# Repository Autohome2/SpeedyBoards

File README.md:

# SpeedyBoards
WTMtronics has developed several EMS PCBs designed to use the Speeduino firmware.
The Speeduino code is available here [Speeduino](https://github.com/noisymime/speeduino), but the easiest way to load the code onto your ECU is to use [SpeedyLoader](https://github.com/speeduino/SpeedyLoader).
## Ocelot
The latest ECU designed by WTMtronics builds on the UA4C that came before it, and in fact if you compare the two side by side you will see many similarities. However there have been many improvements over the previous model which are outlined in the list below.
- Automotive connector
- Reduced size
- Integrated microcontroller
- VSS input
- Flyback diodes
- Reset button

The reset button was added as the only reset connection made to the microcontroller to prevent unwanted resets from USB connected devices. There is a caveat to this arrangement though. While the first time a firmware is loaded it will go on without intervention, subsequent times will require the user to hold the reset button down then release the button when the program starts the upload process. If the upload does not start right away go back and try again.

The Ocelot uses the Silicon Labs CP2102N USB to UART controller chip. Most modern computers will detect and automatically load a driver for the COM port. If you are not getting the COM port, then you can download drivers from their website [Silicon Labs Drivers](https://www.silabs.com/developers/usb-to-uart-bridge-vcp-drivers).

Versions:

A4:
- Corrected USB chip power
- Changed to smaller USB chip
- Corrected trigger labeling
- Changed trigger jumpers to match other boards

A3:
- First release

### Errata
vA3:
- Labeling for trigger jumpers is reversed. The secondary trigger jumpers are nearest the outside edge of the board, and the primary trigger jumpers are near the trigger conditioner socket.
- Serial numbers prior to 002287 will not operate with out a USB connection if no Bluetooth adapter is attached. If your serial number is 002287 or higher this issue does not affect your unit. If you are affected by this issue, please contact us so we can help you [WTMtronics Help](https://wtmtronics.com/help).
## UA4C
The Under Arduino Four Channel was designed to be as small as possible wile still using a standard off the shelf Arduino MEGA and Hammond extruded enclosure. This was achieved by using SMD components and placing the Arduino upside-down on top of the PCB. The unique stacking arrangement allows the unit to be particularly thin for a unit that still uses a separate Arduino MEGA. It is a 4+4 board that incorporates the follow features.
- Four injector channels
- Four ignitor channels
- Outputs for VVT, 2x PWM idle, boost, fuel pump, tachometer, and 2x fan
- Four auxiliary outputs
- Built in stepper idle control (versions C)
- Two trigger inputs
- Launch input
- Two additional interrupt input designated as flex and knock*
- Analog inputs for CLT, IAT, TPS, and O2
- Two auxiliary analog inputs
- MAP and baro sensor onboard
- Two GPIO connections that breakout inside the case

Latest version: C6

*Knock is currently unsupported in the firmware. Either input can be used for VSS.
## NO2C
The No Overhang Two Channel was designed to incorporate as many features as possible into a through-hole board that does not exceed the dimensions of the Arduino MEGA microcontroller it sits on top of. It is a 2+2 channel board that incorporates the features below.
- Two injector channels
- Two ignitor channels
- Outputs for VVT PWM idle, boost, fuel pump, and tachometer
- Two trigger inputs
- Launch input
- Analog inputs for CLT, IAT, TPS, and O2
- MAP sensor onboard
- Socket for stepper idle control module

Latest version: D1

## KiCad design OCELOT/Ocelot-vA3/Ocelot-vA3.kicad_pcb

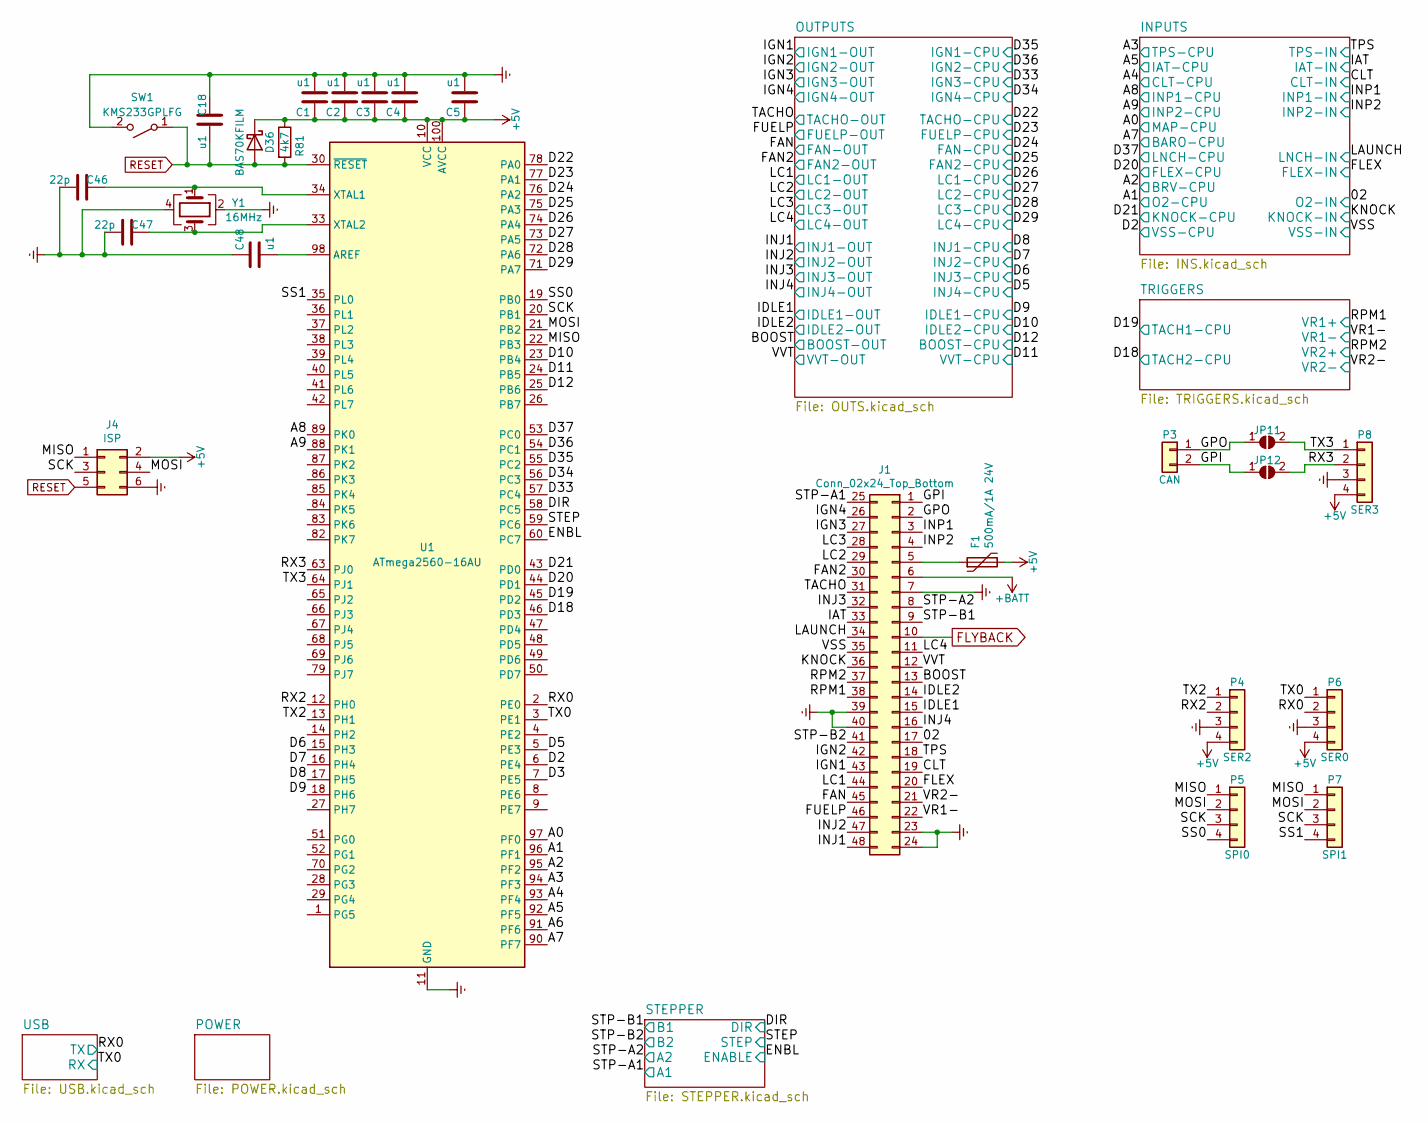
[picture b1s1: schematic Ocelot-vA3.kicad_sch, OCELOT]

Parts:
C1, C2, C3, C4, C5, C18, C48: u1; C_0603_1608Metric; MPN CL21B104KBFNNNE
C46, C47: 22p; C_0603_1608Metric
D36: BAS70KFILM; D_SOD-523; MPN BAS70-02V-V-G-08
F1: 500mA/1A 24V; Fuse_1206_3216Metric; MPN 0ZCJ0050AF2E
J1: Conn_02x24_Top_Bottom; JSA_ZRO_48_Black
J4: ISP; PinHeader_2x03_P2.54mm_Vertical
JP11, JP12: SolderJumper_2_Open; SolderJumper-2_P1.3mm_Open_Pad1.0x1.5mm; MPN DNP
P3: CAN; PinHeader_1x02_P2.54mm_Vertical; MPN DNP
P4: SER2; Pin_Header_Straight_1x04_Pitch2.54mm; MPN DNP
P5: SPI0; Pin_Header_Straight_1x04_Pitch2.54mm; MPN DNP
P6: SER0; Pin_Header_Straight_1x04_Pitch2.54mm; MPN DNP
P7: SPI1; Pin_Header_Straight_1x04_Pitch2.54mm; MPN DNP
P8: SER3; Pin_Header_Straight_1x04_Pitch2.54mm; MPN DNP
R81: 4k7; R_0603_1608Metric
SW1: KMS233GPLFG; SW_SPST_CK_KMS2xxGP
U1: ATmega2560-16AU; TQFP-100_14x14mm_P0.5mm
Y1: 16MHz; Crystal_SMD_3225-4Pin_3.2x2.5mm; MPN YSX321SL

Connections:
+5V: C1.1, C2.1, C3.1, C4.1, C5.1, D36.1 (K), F1.2, J4.2, P4.4, P6.4, P8.4, R81.1, U1.10 (VCC), U1.31 (VCC), U1.61 (VCC), U1.80 (VCC), U1.100 (AVCC); also elsewhere on the board
+BATT: J1.6; also elsewhere on the board
/02: J1.17; also elsewhere on the board
/A0: U1.97 (PF0); also elsewhere on the board
/A1: U1.96 (PF1); also elsewhere on the board
/A2: U1.95 (PF2); also elsewhere on the board
/A3: U1.94 (PF3); also elsewhere on the board
/A4: U1.93 (PF4); also elsewhere on the board
/A5: U1.92 (PF5); also elsewhere on the board
/A6: U1.91 (PF6)
/A7: U1.90 (PF7); also elsewhere on the board
/A8: U1.89 (PK0); also elsewhere on the board
/A9: U1.88 (PK1); also elsewhere on the board
/BOOST: J1.13; also elsewhere on the board
/CLT: J1.19; also elsewhere on the board
/D2: U1.6 (PE4); also elsewhere on the board
/D3: U1.7 (PE5)
/D5: U1.5 (PE3); also elsewhere on the board
/D6: U1.15 (PH3); also elsewhere on the board
/D7: U1.16 (PH4); also elsewhere on the board
/D8: U1.17 (PH5); also elsewhere on the board
/D9: U1.18 (PH6); also elsewhere on the board
/D10: U1.23 (PB4); also elsewhere on the board
/D11: U1.24 (PB5); also elsewhere on the board
/D12: U1.25 (PB6); also elsewhere on the board
/D18: U1.46 (PD3); also elsewhere on the board
/D19: U1.45 (PD2); also elsewhere on the board
/D20: U1.44 (PD1); also elsewhere on the board
/D21: U1.43 (PD0); also elsewhere on the board
/D22: U1.78 (PA0); also elsewhere on the board
/D23: U1.77 (PA1); also elsewhere on the board
/D24: U1.76 (PA2); also elsewhere on the board
/D25: U1.75 (PA3); also elsewhere on the board
/D26: U1.74 (PA4); also elsewhere on the board
/D27: U1.73 (PA5); also elsewhere on the board
/D28: U1.72 (PA6); also elsewhere on the board
/D29: U1.71 (PA7); also elsewhere on the board
/D33: U1.57 (PC4); also elsewhere on the board
/D34: U1.56 (PC3); also elsewhere on the board
/D35: U1.55 (PC2); also elsewhere on the board
/D36: U1.54 (PC1); also elsewhere on the board
/D37: U1.53 (PC0); also elsewhere on the board
/DIR: U1.58 (PC5); also elsewhere on the board
/ENBL: U1.60 (PC7); also elsewhere on the board
/FAN: J1.45; also elsewhere on the board
/FAN2: J1.30; also elsewhere on the board
/FLEX: J1.20; also elsewhere on the board
/FUELP: J1.46; also elsewhere on the board
/GPI: J1.1, JP12.1 (A), P3.2
/GPO: J1.2, JP11.1 (A), P3.1
/IAT: J1.33; also elsewhere on the board
/IDLE1: J1.15; also elsewhere on the board
/IDLE2: J1.14; also elsewhere on the board
/IGN1: J1.43; also elsewhere on the board
/IGN2: J1.42; also elsewhere on the board
/IGN3: J1.27; also elsewhere on the board
/IGN4: J1.26; also elsewhere on the board
/INJ1: J1.48; also elsewhere on the board
/INJ2: J1.47; also elsewhere on the board
/INJ3: J1.32; also elsewhere on the board
/INJ4: J1.16; also elsewhere on the board
/INP1: J1.3; also elsewhere on the board
/INP2: J1.4; also elsewhere on the board
/KNOCK: J1.36; also elsewhere on the board
/LAUNCH: J1.34; also elsewhere on the board
/LC1: J1.44; also elsewhere on the board
/LC2: J1.29; also elsewhere on the board
/LC3: J1.28; also elsewhere on the board
/LC4: J1.11; also elsewhere on the board
/MISO: J4.1, P5.1, P7.1, U1.22 (PB3)
/MOSI: J4.4, P5.2, P7.2, U1.21 (PB2)
/RPM1: J1.38; also elsewhere on the board
/RPM2: J1.37; also elsewhere on the board
/RX0: P6.2, U1.2 (PE0); also elsewhere on the board
/RX2: P4.2, U1.12 (PH0)
/RX3: JP12.2 (B), P8.2, U1.63 (PJ0)
/SCK: J4.3, P5.3, P7.3, U1.20 (PB1)
/SS0: P5.4, U1.19 (PB0)
/SS1: P7.4, U1.35 (PL0)
/STEP: U1.59 (PC6); also elsewhere on the board
/STP-A1: J1.25; also elsewhere on the board
/STP-A2: J1.8; also elsewhere on the board
/STP-B1: J1.9; also elsewhere on the board
/STP-B2: J1.41; also elsewhere on the board
/TACHO: J1.31; also elsewhere on the board
/TPS: J1.18; also elsewhere on the board
/TX0: P6.1, U1.3 (PE1); also elsewhere on the board
/TX2: P4.1, U1.13 (PH1)
/TX3: JP11.2 (B), P8.1, U1.64 (PJ1)
/VR1-: J1.22; also elsewhere on the board
/VR2-: J1.21; also elsewhere on the board
/VSS: J1.35; also elsewhere on the board
/VVT: J1.12; also elsewhere on the board
Earth: C1.2, C2.2, C3.2, C4.2, C5.2, C18.1, C46.2, C47.1, C48.1, J1.7, J1.23, J1.24, J1.39, J1.40, J4.6, P4.3, P6.3, P8.3, SW1.2 (B), U1.11 (GND), U1.32 (GND), U1.62 (GND), U1.81 (GND), U1.99 (GND), Y1.2, Y1.4; also elsewhere on the board
FLYBACK: J1.10; also elsewhere on the board
unnamed: F1.1, J1.5
unnamed: C48.2, U1.98 (AREF)
unnamed: C46.1, U1.34 (XTAL1), Y1.1
unnamed: C47.2, U1.33 (XTAL2), Y1.3
RESET: C18.2, D36.2 (A), J4.5, R81.2, SW1.1 (A), U1.30 (~RESET)

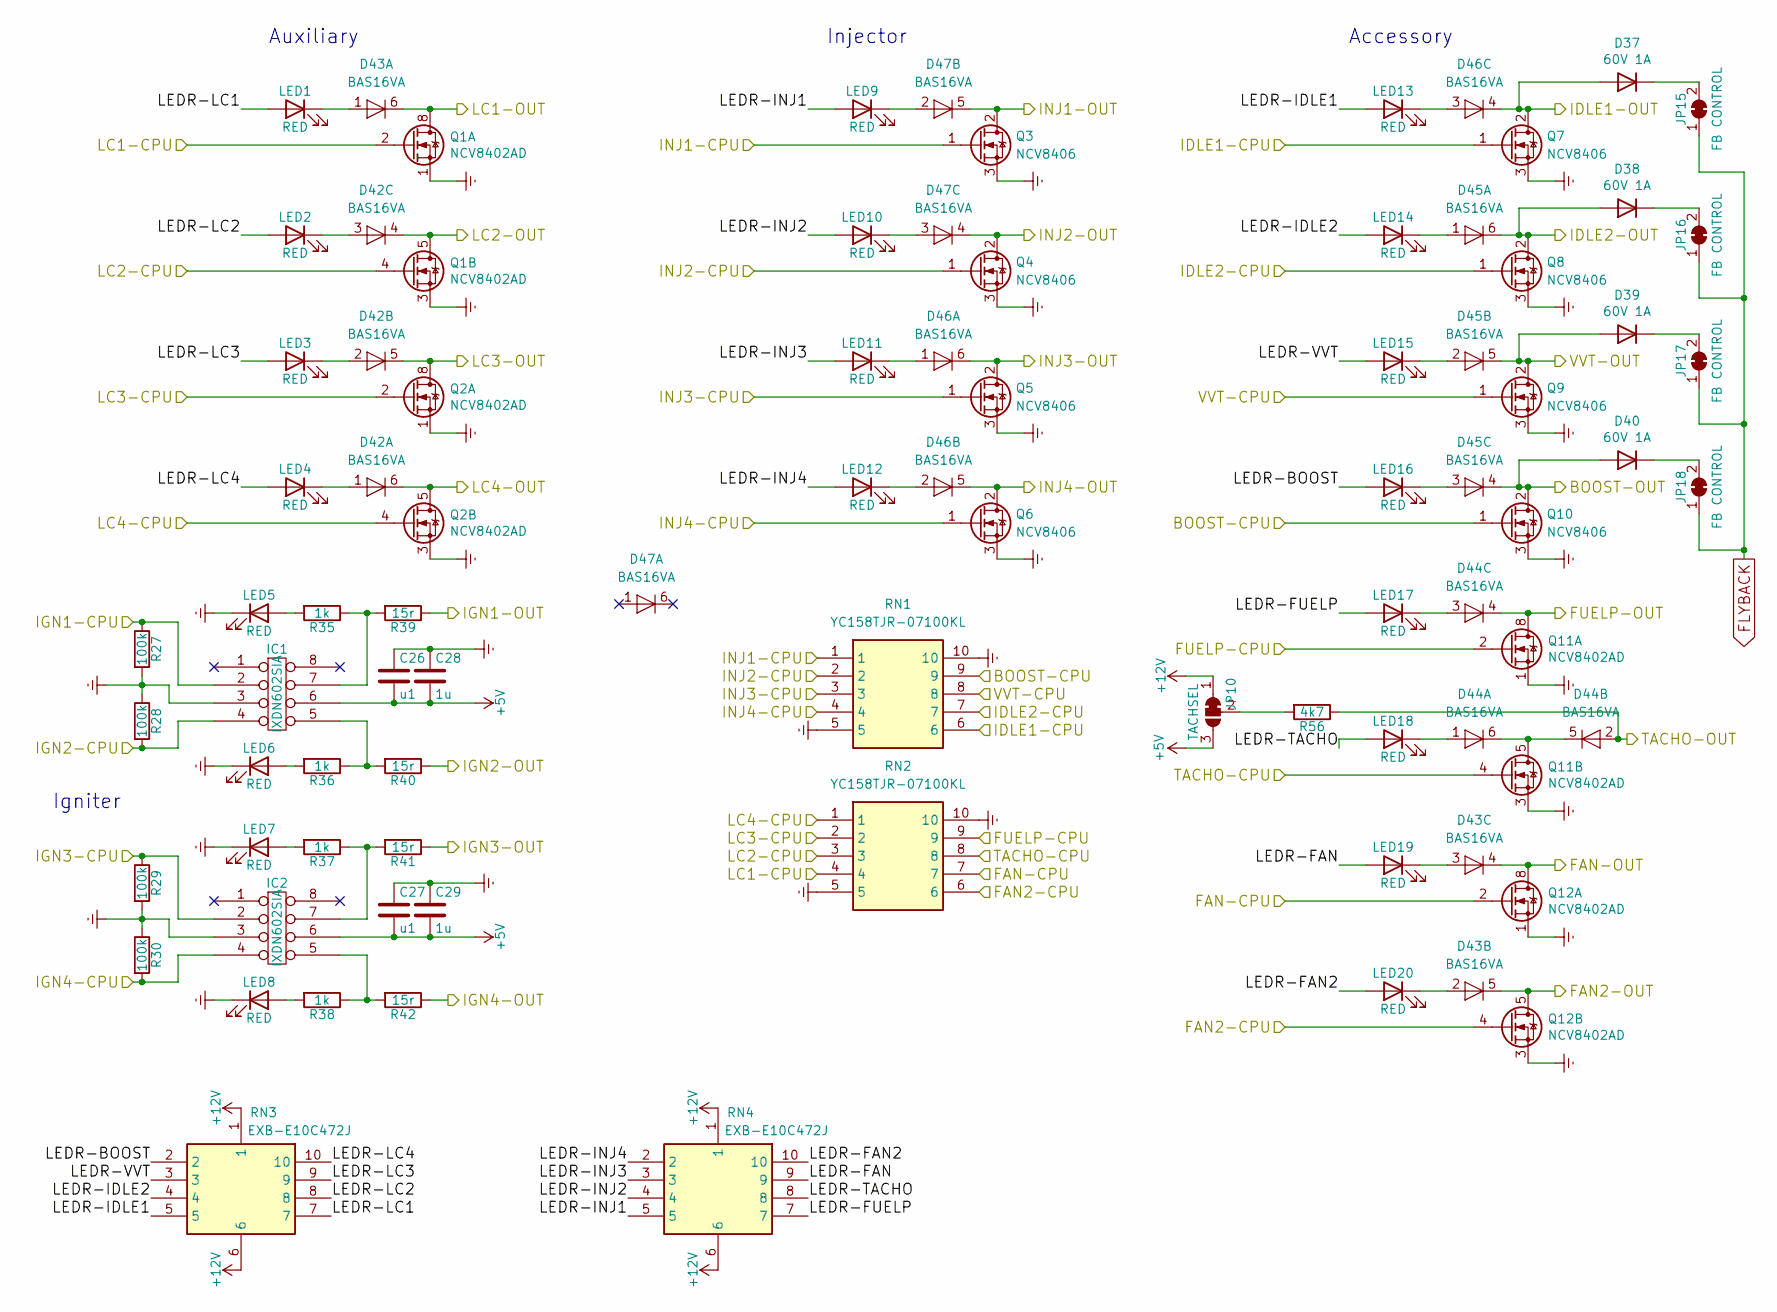
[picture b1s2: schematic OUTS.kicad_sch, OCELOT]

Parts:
C26, C27: u1; C_0603_1608Metric; MPN CL21B104KBFNNNE
C28, C29: 1u; C_0603_1608Metric; MPN CL21B105KBFNNNE
D37, D38, D39, D40: 60V 1A; D_SOD-123F
D42, D43, D44, D45, D46, D47: BAS16VA; SOT-563
IC1, IC2: IXDN602SIA; SOIC-8_3.9x4.9mm_P1.27mm; MPN IXDN602SIA
JP10: TACHSEL; SolderJumper-3_P1.3mm_Bridged12_Pad1.0x1.5mm_NumberLabels; MPN DNP
JP15, JP16, JP17, JP18: FB CONTROL; SolderJumper-2_P1.3mm_Bridged_Pad1.0x1.5mm; MPN DNP
LED1, LED2, LED3, LED4, LED5, LED6, LED7, LED8, LED9, LED10, LED11, LED12, LED13, LED14, LED15, LED16, LED17, LED18, LED19, LED20: RED; LED_0402_1005Metric; MPN SML-310LTT86
Q1, Q2, Q11, Q12: NCV8402AD; SOIC-8_3.9x4.9mm_P1.27mm; MPN NCV8402ADDR2G
Q3, Q4, Q5, Q6, Q7, Q8, Q9, Q10: NCV8406; TO-252-3_TabPin2; MPN NCV8406BDTRKG
R27, R28, R29, R30: 100k; R_0402_1005Metric; MPN RK73B1JTTD104J
R35, R36, R37, R38: 1k; R_0603_1608Metric; MPN RK73H2ATTD4700F
R39, R40, R41, R42: 15r; R_2512_6332Metric; MPN RK73H3ATTE15R0F
R56: 4k7; R_0603_1608Metric
RN1, RN2: YC158TJR-07100KL; YC158TJR07100KL; Manufacturer_Part_Number YC158TJR-07100KL
RN3, RN4: EXB-E10C472J; EXBE10C473J; Manufacturer_Part_Number EXB-E10C473J; Mouser Part Number 667-EXB-E10C473J

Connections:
+5V: C26.2, C27.2, C28.2, C29.2, IC1.6, IC2.6, JP10.3 (B); also elsewhere on the board
+12V: JP10.1 (A), RN3.1, RN3.6, RN4.1, RN4.6; also elsewhere on the board
/BOOST: D40.2 (A), D45.4 (K), Q10.2 (D); also elsewhere on the board
/D5: Q6.1 (G), RN1.4; also elsewhere on the board
/D6: Q5.1 (G), RN1.3; also elsewhere on the board
/D7: Q4.1 (G), RN1.2; also elsewhere on the board
/D8: Q3.1 (G), RN1.1; also elsewhere on the board
/D9: Q7.1 (G), RN1.6; also elsewhere on the board
/D10: Q8.1 (G), RN1.7; also elsewhere on the board
/D11: Q9.1 (G), RN1.8; also elsewhere on the board
/D12: Q10.1 (G), RN1.9; also elsewhere on the board
/D22: Q11.4 (G2), RN2.8; also elsewhere on the board
/D23: Q11.2 (G1), RN2.9; also elsewhere on the board
/D24: Q12.2 (G1), RN2.7; also elsewhere on the board
/D25: Q12.4 (G2), RN2.6; also elsewhere on the board
/D26: Q1.2 (G1), RN2.4; also elsewhere on the board
/D27: Q1.4 (G2), RN2.3; also elsewhere on the board
/D28: Q2.2 (G1), RN2.2; also elsewhere on the board
/D29: Q2.4 (G2), RN2.1; also elsewhere on the board
/D33: IC2.2, R29.1; also elsewhere on the board
/D34: IC2.4, R30.2; also elsewhere on the board
/D35: IC1.2, R27.1; also elsewhere on the board
/D36: IC1.4, R28.2; also elsewhere on the board
/FAN: D43.4 (K), Q12.7 (D1), Q12.8 (D1); also elsewhere on the board
/FAN2: D43.5 (K), Q12.5 (D2), Q12.6 (D2); also elsewhere on the board
/FUELP: D44.4 (K), Q11.7 (D1), Q11.8 (D1); also elsewhere on the board
/IDLE1: D37.2 (A), D46.4 (K), Q7.2 (D); also elsewhere on the board
/IDLE2: D38.2 (A), D45.6 (K), Q8.2 (D); also elsewhere on the board
/IGN1: R39.1; also elsewhere on the board
/IGN2: R40.1; also elsewhere on the board
/IGN3: R41.1; also elsewhere on the board
/IGN4: R42.1; also elsewhere on the board
/INJ1: D47.5 (K), Q3.2 (D); also elsewhere on the board
/INJ2: D47.4 (K), Q4.2 (D); also elsewhere on the board
/INJ3: D46.6 (K), Q5.2 (D); also elsewhere on the board
/INJ4: D46.5 (K), Q6.2 (D); also elsewhere on the board
/LC1: D43.6 (K), Q1.7 (D1), Q1.8 (D1); also elsewhere on the board
/LC2: D42.4 (K), Q1.5 (D2), Q1.6 (D2); also elsewhere on the board
/LC3: D42.5 (K), Q2.7 (D1), Q2.8 (D1); also elsewhere on the board
/LC4: D42.6 (K), Q2.5 (D2), Q2.6 (D2); also elsewhere on the board
/OUTPUTS/LEDR-BOOST: LED16.2 (A), RN3.2
/OUTPUTS/LEDR-FAN: LED19.2 (A), RN4.9
/OUTPUTS/LEDR-FAN2: LED20.2 (A), RN4.10
/OUTPUTS/LEDR-FUELP: LED17.2 (A), RN4.7
/OUTPUTS/LEDR-IDLE1: LED13.2 (A), RN3.5
/OUTPUTS/LEDR-IDLE2: LED14.2 (A), RN3.4
/OUTPUTS/LEDR-INJ1: LED9.2 (A), RN4.5
/OUTPUTS/LEDR-INJ2: LED10.2 (A), RN4.4
/OUTPUTS/LEDR-INJ3: LED11.2 (A), RN4.3
/OUTPUTS/LEDR-INJ4: LED12.2 (A), RN4.2
/OUTPUTS/LEDR-LC1: LED1.2 (A), RN3.7
/OUTPUTS/LEDR-LC2: LED2.2 (A), RN3.8
/OUTPUTS/LEDR-LC3: LED3.2 (A), RN3.9
/OUTPUTS/LEDR-LC4: LED4.2 (A), RN3.10
/OUTPUTS/LEDR-TACHO: LED18.2 (A), RN4.8
/OUTPUTS/LEDR-VVT: LED15.2 (A), RN3.3
/TACHO: D44.2 (A), R56.1; also elsewhere on the board
/VVT: D39.2 (A), D45.5 (K), Q9.2 (D); also elsewhere on the board
Earth: C26.1, C27.1, C28.1, C29.1, IC1.3, IC2.3, LED5.1 (K), LED6.1 (K), LED7.1 (K), LED8.1 (K), Q1.1 (S1), Q1.3 (S2), Q2.1 (S1), Q2.3 (S2), Q3.3 (S), Q4.3 (S), Q5.3 (S), Q6.3 (S), Q7.3 (S), Q8.3 (S), Q9.3 (S), Q10.3 (S), Q11.1 (S1), Q11.3 (S2), Q12.1 (S1), Q12.3 (S2), R27.2, R28.1, R29.2, R30.1, RN1.5, RN1.10, RN2.5, RN2.10; also elsewhere on the board
FLYBACK: JP15.1 (A), JP16.1 (A), JP17.1 (A), JP18.1 (A); also elsewhere on the board
unnamed: D37.1 (K), JP15.2 (B)
unnamed: D38.1 (K), JP16.2 (B)
unnamed: D39.1 (K), JP17.2 (B)
unnamed: D40.1 (K), JP18.2 (B)
unnamed: D42.1 (A), LED4.1 (K)
unnamed: D42.2 (A), LED3.1 (K)
unnamed: D42.3 (A), LED2.1 (K)
unnamed: D43.1 (A), LED1.1 (K)
unnamed: D43.2 (A), LED20.1 (K)
unnamed: D43.3 (A), LED19.1 (K)
unnamed: D44.1 (A), LED18.1 (K)
unnamed: D44.5 (K), D44.6 (K), Q11.5 (D2), Q11.6 (D2)
unnamed: D44.3 (A), LED17.1 (K)
unnamed: D45.1 (A), LED14.1 (K)
unnamed: D45.2 (A), LED15.1 (K)
unnamed: D45.3 (A), LED16.1 (K)
unnamed: D46.1 (A), LED11.1 (K)
unnamed: D46.2 (A), LED12.1 (K)
unnamed: D46.3 (A), LED13.1 (K)
unnamed: D47.2 (A), LED9.1 (K)
unnamed: D47.3 (A), LED10.1 (K)
unnamed: IC1.5, R36.1, R40.2
unnamed: IC1.7, R35.1, R39.2
unnamed: IC2.5, R38.1, R42.2
unnamed: IC2.7, R37.1, R41.2
unnamed: JP10.2 (C), R56.2
unnamed: LED5.2 (A), R35.2
unnamed: LED6.2 (A), R36.2
unnamed: LED7.2 (A), R37.2
unnamed: LED8.2 (A), R38.2

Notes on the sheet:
Auxiliary
Injector
Accessory
Igniter

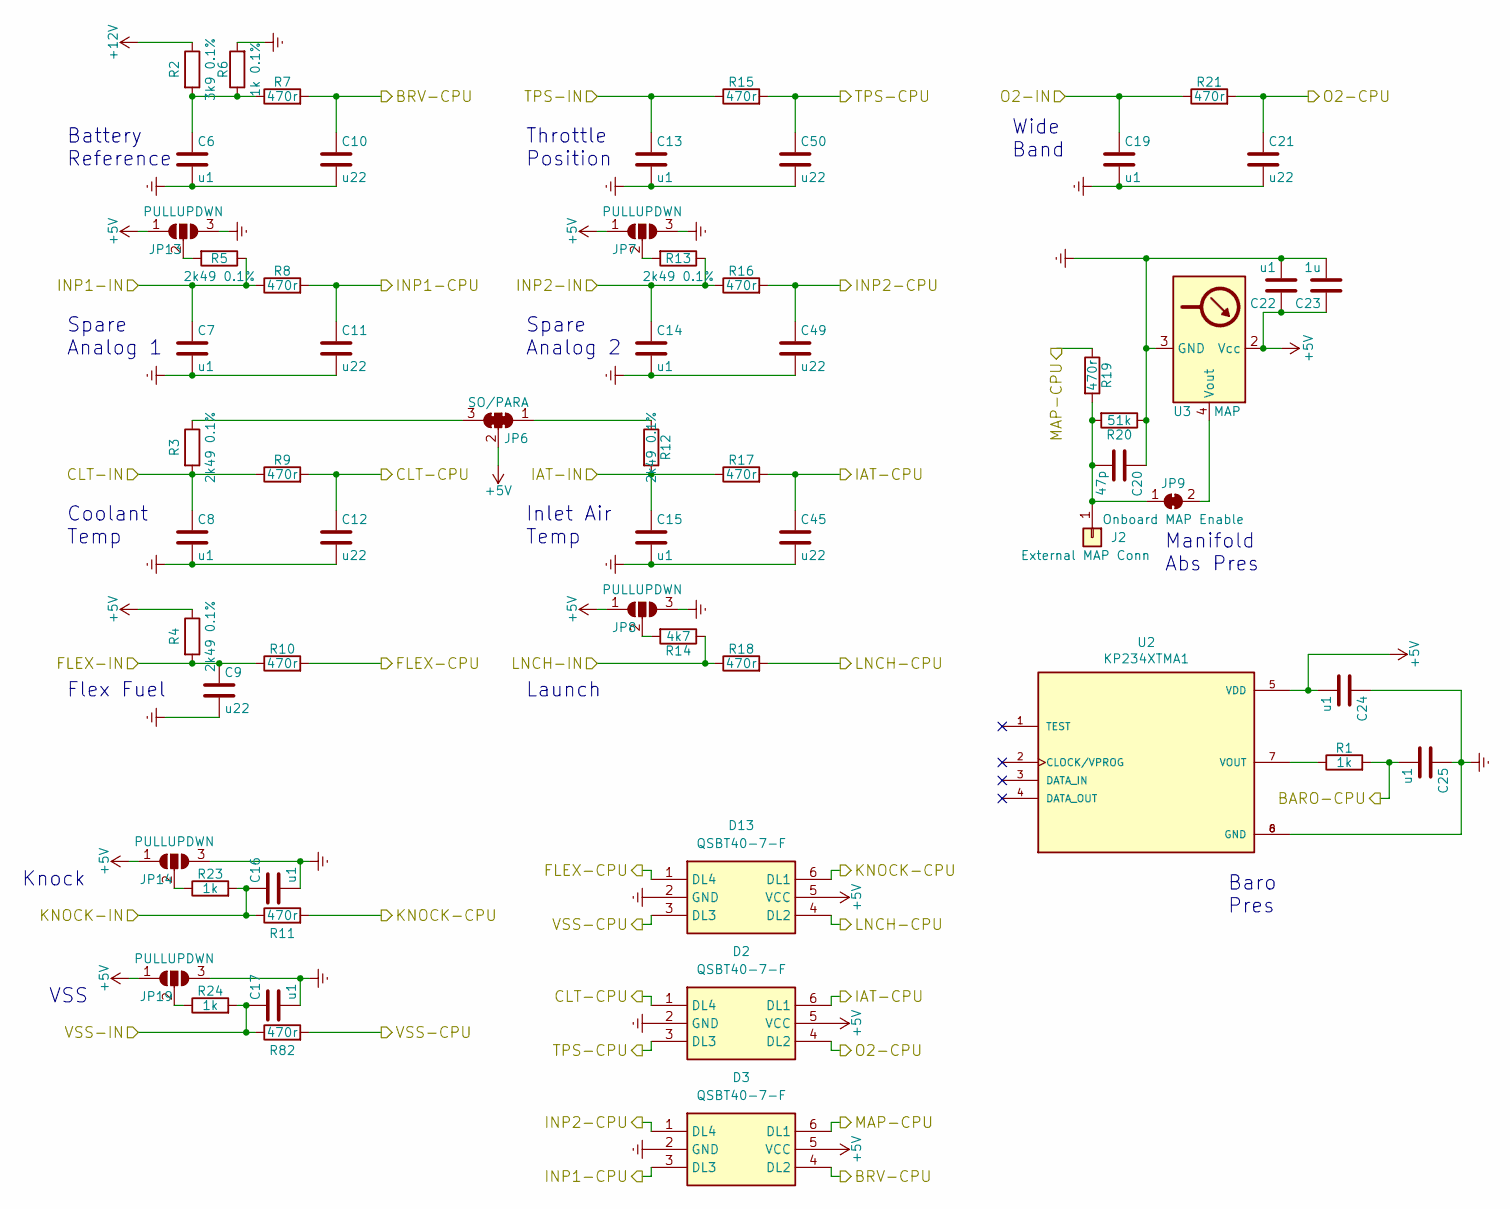
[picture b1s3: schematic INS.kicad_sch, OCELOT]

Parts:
C6, C7, C8, C13, C14, C15, C16, C17, C19, C22, C24, C25: u1; C_0603_1608Metric; MPN CL21B104KBFNNNE
C9, C10, C11, C12, C21, C45, C49, C50: u22; C_0603_1608Metric; MPN CL21B224KBFNNNE
C20: 47p; C_0603_1608Metric; MPN CL21C470JBANNNC
C23: 1u; C_0603_1608Metric; MPN CL21B105KBFNNNE
D2, D3, D13: QSBT40-7-F; SOT-363_SC-70-6; Mouser Part Number 621-QSBT40-F
J2: External MAP Conn; SolderWirePad_single_1mmDrill; MPN DNP
JP6: SO/PARA; SolderJumper-3_P1.3mm_Bridged123_Pad1.0x1.5mm_NumberLabels; MPN DNP
JP7, JP8, JP13, JP14, JP19: PULLUPDWN; SolderJumper-3_P1.3mm_Open_Pad1.0x1.5mm_NumberLabels; MPN DNP
JP9: Onboard MAP Enable; SolderJumper-2_P1.3mm_Bridged_Pad1.0x1.5mm; MPN DNP
R1, R23, R24: 1k; R_0603_1608Metric; MPN RK73H2ATTD1001F
R2: 3k9 0.1%; R_0805_2012Metric; MPN ERA6AEB392V
R3, R4, R5, R12, R13: 2k49 0.1%; R_0805_2012Metric; MPN ERA6AEB2491V
R6: 1k 0.1%; R_0805_2012Metric; MPN ERA6AEB102V
R7, R8, R9, R10, R11, R15, R16, R17, R18, R19, R21, R82: 470r; R_0805_2012Metric; MPN RK73H2ATTD4700F
R14: 4k7; R_0603_1608Metric
R20: 51k; R_0402_1005Metric; MPN RK73H2ATTD5102F
U2: KP234XTMA1; XDCR_KP234XTMA1; PARTREV 1.0
U3: MAP; Freescale_98ARH99089A; MPN MPXH6400AC6U

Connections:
+5V: C22.1, C23.1, C24.2, D2.5 (VCC), D3.5 (VCC), D13.5 (VCC), JP6.2 (C), JP7.1 (A), JP8.1 (A), JP13.1 (A), JP14.1 (A), JP19.1 (A), R4.1, U2.5 (VDD), U3.2 (Vcc); also elsewhere on the board
+12V: R2.1; also elsewhere on the board
/02: C19.1, R21.1; also elsewhere on the board
/A0: D3.6 (DL1), R19.1; also elsewhere on the board
/A1: C21.1, D2.4 (DL2), R21.2; also elsewhere on the board
/A2: C10.1, D3.4 (DL2), R7.2; also elsewhere on the board
/A3: C50.1, D2.3 (DL3), R15.2; also elsewhere on the board
/A4: C12.1, D2.1 (DL4), R9.2; also elsewhere on the board
/A5: C45.1, D2.6 (DL1), R17.2; also elsewhere on the board
/A7: C25.2, R1.2; also elsewhere on the board
/A8: C11.1, D3.3 (DL3), R8.2; also elsewhere on the board
/A9: C49.1, D3.1 (DL4), R16.2; also elsewhere on the board
/CLT: C8.1, R3.2, R9.1; also elsewhere on the board
/D2: D13.3 (DL3), R82.2; also elsewhere on the board
/D20: D13.1 (DL4), R10.2; also elsewhere on the board
/D21: D13.6 (DL1), R11.2; also elsewhere on the board
/D37: D13.4 (DL2), R18.2; also elsewhere on the board
/FLEX: C9.1, R4.2, R10.1; also elsewhere on the board
/IAT: C15.1, R12.2, R17.1; also elsewhere on the board
/INP1: C7.1, R5.1, R8.1; also elsewhere on the board
/INP2: C14.1, R13.1, R16.1; also elsewhere on the board
/KNOCK: C16.1, R11.1, R23.2; also elsewhere on the board
/LAUNCH: R14.1, R18.1; also elsewhere on the board
/TPS: C13.1, R15.1; also elsewhere on the board
/VSS: C17.1, R24.2, R82.1; also elsewhere on the board
Earth: C6.2, C7.2, C8.2, C9.2, C10.2, C11.2, C12.2, C13.2, C14.2, C15.2, C16.2, C17.2, C19.2, C20.1, C21.2, C22.2, C23.2, C24.1, C25.1, C45.2, C49.2, C50.2, D2.2 (GND), D3.2 (GND), D13.2 (GND), JP7.3 (B), JP8.3 (B), JP13.3 (B), JP14.3 (B), JP19.3 (B), R6.2, R20.1, U2.6 (GND), U2.8 (GND), U3.3 (GND); also elsewhere on the board
unnamed: C6.1, R2.2, R6.1, R7.1
unnamed: C20.2, J2.1, JP9.1 (A), R19.2, R20.2
unnamed: JP6.1 (A), R12.1
unnamed: JP6.3 (B), R3.1
unnamed: JP7.2 (C), R13.2
unnamed: JP8.2 (C), R14.2
unnamed: JP9.2 (B), U3.4 (Vout)
unnamed: JP13.2 (C), R5.2
unnamed: JP14.2 (C), R23.1
unnamed: JP19.2 (C), R24.1
unnamed: R1.1, U2.7 (VOUT)

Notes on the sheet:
VSS
Inlet Air Temp
Knock
Coolant Temp
Wide Band
Spare Analog 2
Battery Reference
Spare Analog 1
Flex Fuel
Baro Pres
Manifold Abs Pres
Launch
Throttle Position

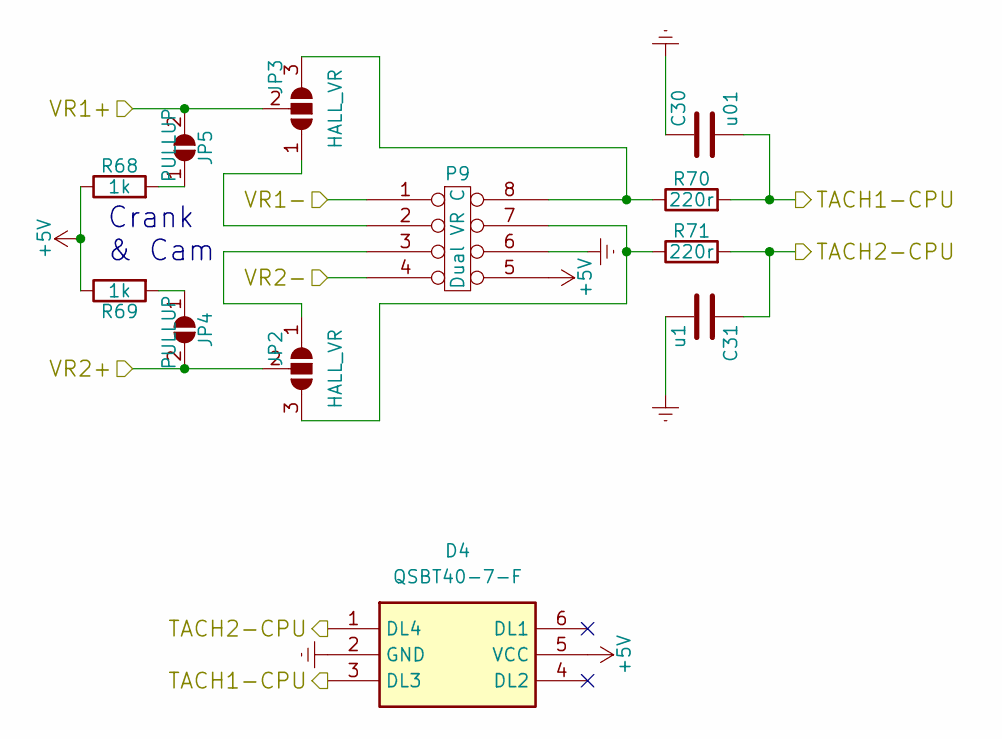
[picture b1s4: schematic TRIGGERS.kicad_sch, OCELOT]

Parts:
C30: u01; C_0603_1608Metric; MPN CL21B103KBCNNNC
C31: u1; C_0603_1608Metric; MPN CL21B104KBFNNNE
D4: QSBT40-7-F; SOT-363_SC-70-6; Mouser Part Number 621-QSBT40-F
JP2, JP3: HALL_VR; JPR_3POS_SMLHL; MPN DNP
JP4, JP5: PULLUP; JPR_2POS_SMLHL; MPN DNP
P9: Dual VR C; DIP-8_W7.62mm_Socket; MPN DNP
R68, R69: 1k; R_0603_1608Metric; MPN RK73H2ATTD1001F
R70, R71: 220r; R_0805_2012Metric; MPN RK73H2ATTD2200F

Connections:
+5V: D4.5 (VCC), P9.5, R68.1, R69.1; also elsewhere on the board
/D18: C31.1, D4.1 (DL4), R71.2; also elsewhere on the board
/D19: C30.2, D4.3 (DL3), R70.2; also elsewhere on the board
/RPM1: JP3.2 (C), JP5.2 (B); also elsewhere on the board
/RPM2: JP2.2 (C), JP4.2 (B); also elsewhere on the board
/VR1-: P9.1; also elsewhere on the board
/VR2-: P9.4; also elsewhere on the board
Earth: C30.1, C31.2, D4.2 (GND), P9.6; also elsewhere on the board
unnamed: JP2.1 (A), P9.3
unnamed: JP2.3 (B), P9.7, R71.1
unnamed: JP3.1 (A), P9.2
unnamed: JP3.3 (B), P9.8, R70.1
unnamed: JP4.1 (A), R69.2
unnamed: JP5.1 (A), R68.2

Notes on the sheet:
Crank & Cam

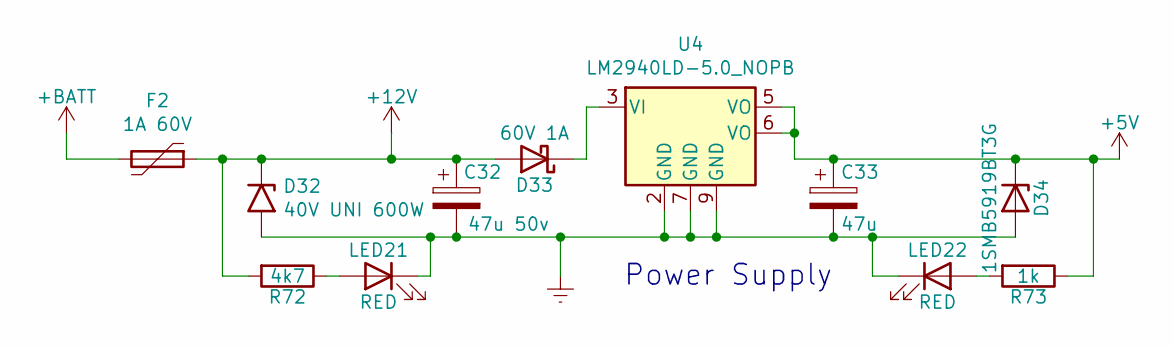
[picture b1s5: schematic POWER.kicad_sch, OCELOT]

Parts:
C32: 47u 50v; CP_Elec_6.3x5.4; MPN EEE-FT1H470AL
C33: 47u; CP_EIA-3216-18_Kemet-A; MPN T55A476M6R3C0200
D32: 40V UNI 600W; D_SMB; MPN SMBJ40A
D33: 60V 1A; D_SOD-123F; MPN SDM160S1FQ-7
D34: 1SMB5919BT3G; D_SMB; MPN 1SMB5919BT3G
F2: 1A 60V; Fuse_2920_7451Metric_Castellated; MPN 0ZCF0100AF2A
LED21, LED22: RED; LED_0402_1005Metric; MPN SML-310LTT86
R72: 4k7; R_0603_1608Metric
R73: 1k; R_0603_1608Metric; MPN RK73H2ATTD4700F
U4: LM2940LD-5.0_NOPB; WSON-8-1EP_4x4mm_P0.8mm_EP2.2x3mm_ThermalVias

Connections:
+5V: C33.1, D34.1 (K), R73.1, U4.5 (VO), U4.6 (VO); also elsewhere on the board
+12V: C32.1, D32.1 (A1), D33.2 (A), F2.1, R72.2; also elsewhere on the board
+BATT: F2.2; also elsewhere on the board
Earth: C32.2, C33.2, D32.2 (A2), D34.2 (A), LED21.1 (K), LED22.1 (K), U4.2 (GND), U4.7 (GND), U4.9 (GND); also elsewhere on the board
unnamed: D33.1 (K), U4.3 (VI)
unnamed: LED21.2 (A), R72.1
unnamed: LED22.2 (A), R73.2

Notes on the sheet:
Power Supply

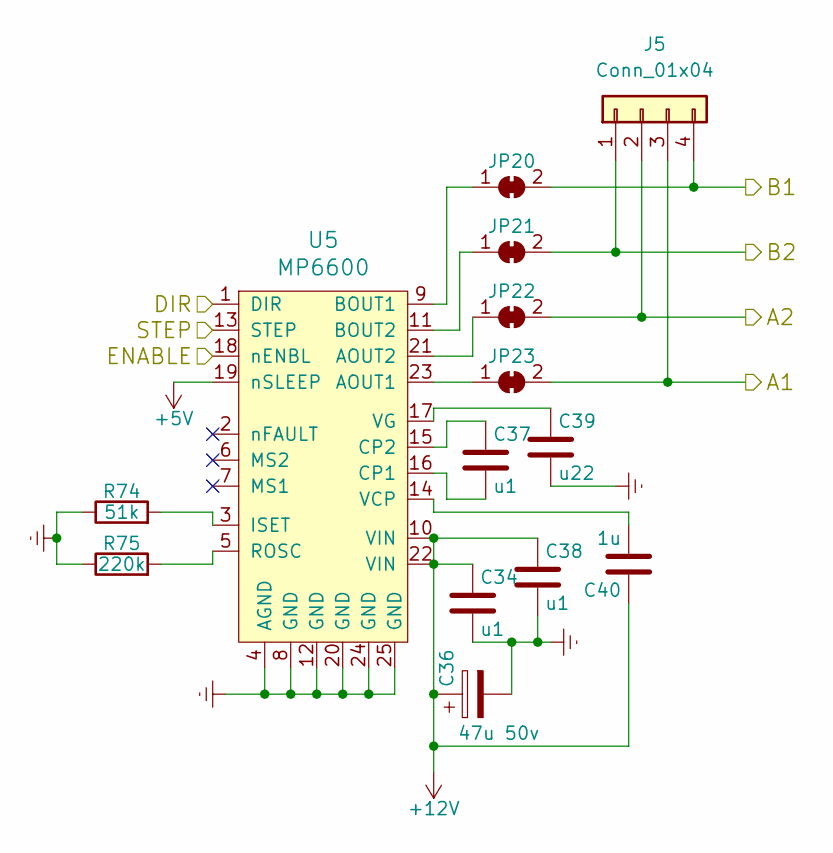
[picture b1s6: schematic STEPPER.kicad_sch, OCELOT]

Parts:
C34, C37, C38: u1; C_0603_1608Metric; MPN CL21B104KBFNNNE
C36: 47u 50v; CP_Elec_6.3x5.4; MPN EEE-FT1H470AL
C39: u22; C_0603_1608Metric; MPN CL21B224KBFNNNE
C40: 1u; C_0603_1608Metric; MPN CL21B105KBFNNNE
J5: Conn_01x04; PinHeader_1x04_P2.00mm_Vertical
JP20, JP21, JP22, JP23: FB CONTROL; SolderJumper-2_P1.3mm_Bridged_Pad1.0x1.5mm_VisibleBridge; MPN DNP
R74: 51k; R_0402_1005Metric; MPN RK73H2ATTD5102F
R75: 220k; R_0402_1005Metric; MPN RK73H2ATTD2203F
U5: MP6600; QFN-24-1EP_4x4mm_P0.5mm_EP2.7x2.7mm_ThermalVias; MPN MP6600GR-Z

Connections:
+5V: U5.19 (nSLEEP); also elsewhere on the board
+12V: C34.1, C36.1, C38.1, C40.1, U5.10 (VIN), U5.22 (VIN); also elsewhere on the board
/DIR: U5.1 (DIR); also elsewhere on the board
/ENBL: U5.18 (nENBL); also elsewhere on the board
/STEP: U5.13 (STEP); also elsewhere on the board
/STP-A1: J5.3, JP23.2 (B); also elsewhere on the board
/STP-A2: J5.2, JP22.2 (B); also elsewhere on the board
/STP-B1: J5.4, JP20.2 (B); also elsewhere on the board
/STP-B2: J5.1, JP21.2 (B); also elsewhere on the board
Earth: C34.2, C36.2, C38.2, C39.2, R74.1, R75.1, U5.4 (AGND), U5.8 (GND), U5.12 (GND), U5.20 (GND), U5.24 (GND), U5.25 (GND); also elsewhere on the board
unnamed: JP20.1 (A), U5.9 (BOUT1)
unnamed: JP21.1 (A), U5.11 (BOUT2)
unnamed: JP22.1 (A), U5.21 (AOUT2)
unnamed: JP23.1 (A), U5.23 (AOUT1)
unnamed: C37.2, U5.16 (CP1)
unnamed: C37.1, U5.15 (CP2)
unnamed: R74.2, U5.3 (ISET)
unnamed: R75.2, U5.5 (ROSC)
unnamed: C40.2, U5.14 (VCP)
unnamed: C39.1, U5.17 (VG)

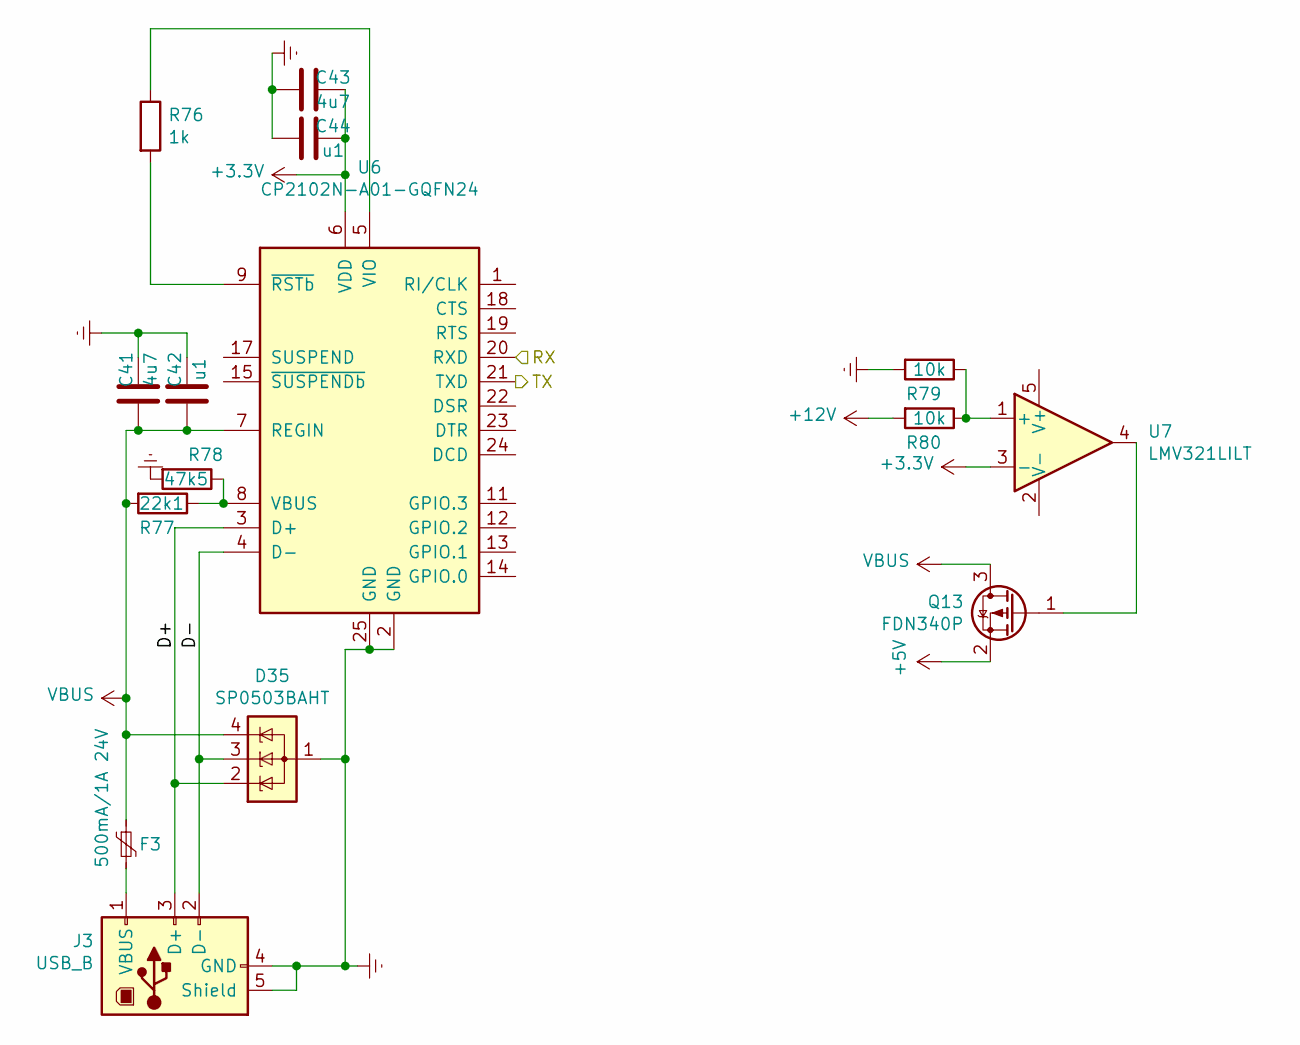
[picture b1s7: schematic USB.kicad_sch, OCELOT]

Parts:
C41, C43: 4u7; C_0603_1608Metric
C42, C44: u1; C_0603_1608Metric
D35: SP0503BAHT; SOT-143
F3: 500mA/1A 24V; Fuse_1206_3216Metric; MPN 0ZCJ0050AF2E
J3: USB_B; USB_B_JST_UBB-4R-D14T-4D_Horizontal
Q13: FDN340P; SOT-23
R76: 1k; R_0603_1608Metric
R77: 22k1; R_0402_1005Metric
R78: 47k5; R_0402_1005Metric
R79, R80: 10k; R_0603_1608Metric
U6: CP2102N-A01-GQFN24; QFN-24-1EP_4x4mm_P0.5mm_EP2.6x2.6mm_ThermalVias
U7: LMV321LILT; SOT-23-5

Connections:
+3V3: C43.1, C44.1, U6.6 (VDD), U7.3 (-)
+5V: Q13.2 (S); also elsewhere on the board
+12V: R80.2; also elsewhere on the board
/RX0: U6.21 (TXD); also elsewhere on the board
/TX0: U6.20 (RXD); also elsewhere on the board
/USB/D+: D35.2 (K), J3.3 (D+), U6.3 (D+)
/USB/D-: D35.3 (K), J3.2 (D-), U6.4 (D-)
Earth: C41.1, C42.1, C43.2, C44.2, D35.1 (A), J3.4 (GND), J3.5 (Shield), R78.2, R79.2, U6.2 (GND), U6.25 (GND); also elsewhere on the board
unnamed: F3.2, J3.1 (VBUS)
unnamed: Q13.1 (G), U7.4
unnamed: R77.1, R78.1, U6.8 (VBUS)
unnamed: R76.1, U6.5 (VIO)
unnamed: R76.2, U6.9 (~RSTb)
unnamed: R79.1, R80.1, U7.1 (+)
VBUS: C41.2, C42.2, D35.4 (K), F3.1, Q13.3 (D), R77.2, U6.7 (REGIN)
